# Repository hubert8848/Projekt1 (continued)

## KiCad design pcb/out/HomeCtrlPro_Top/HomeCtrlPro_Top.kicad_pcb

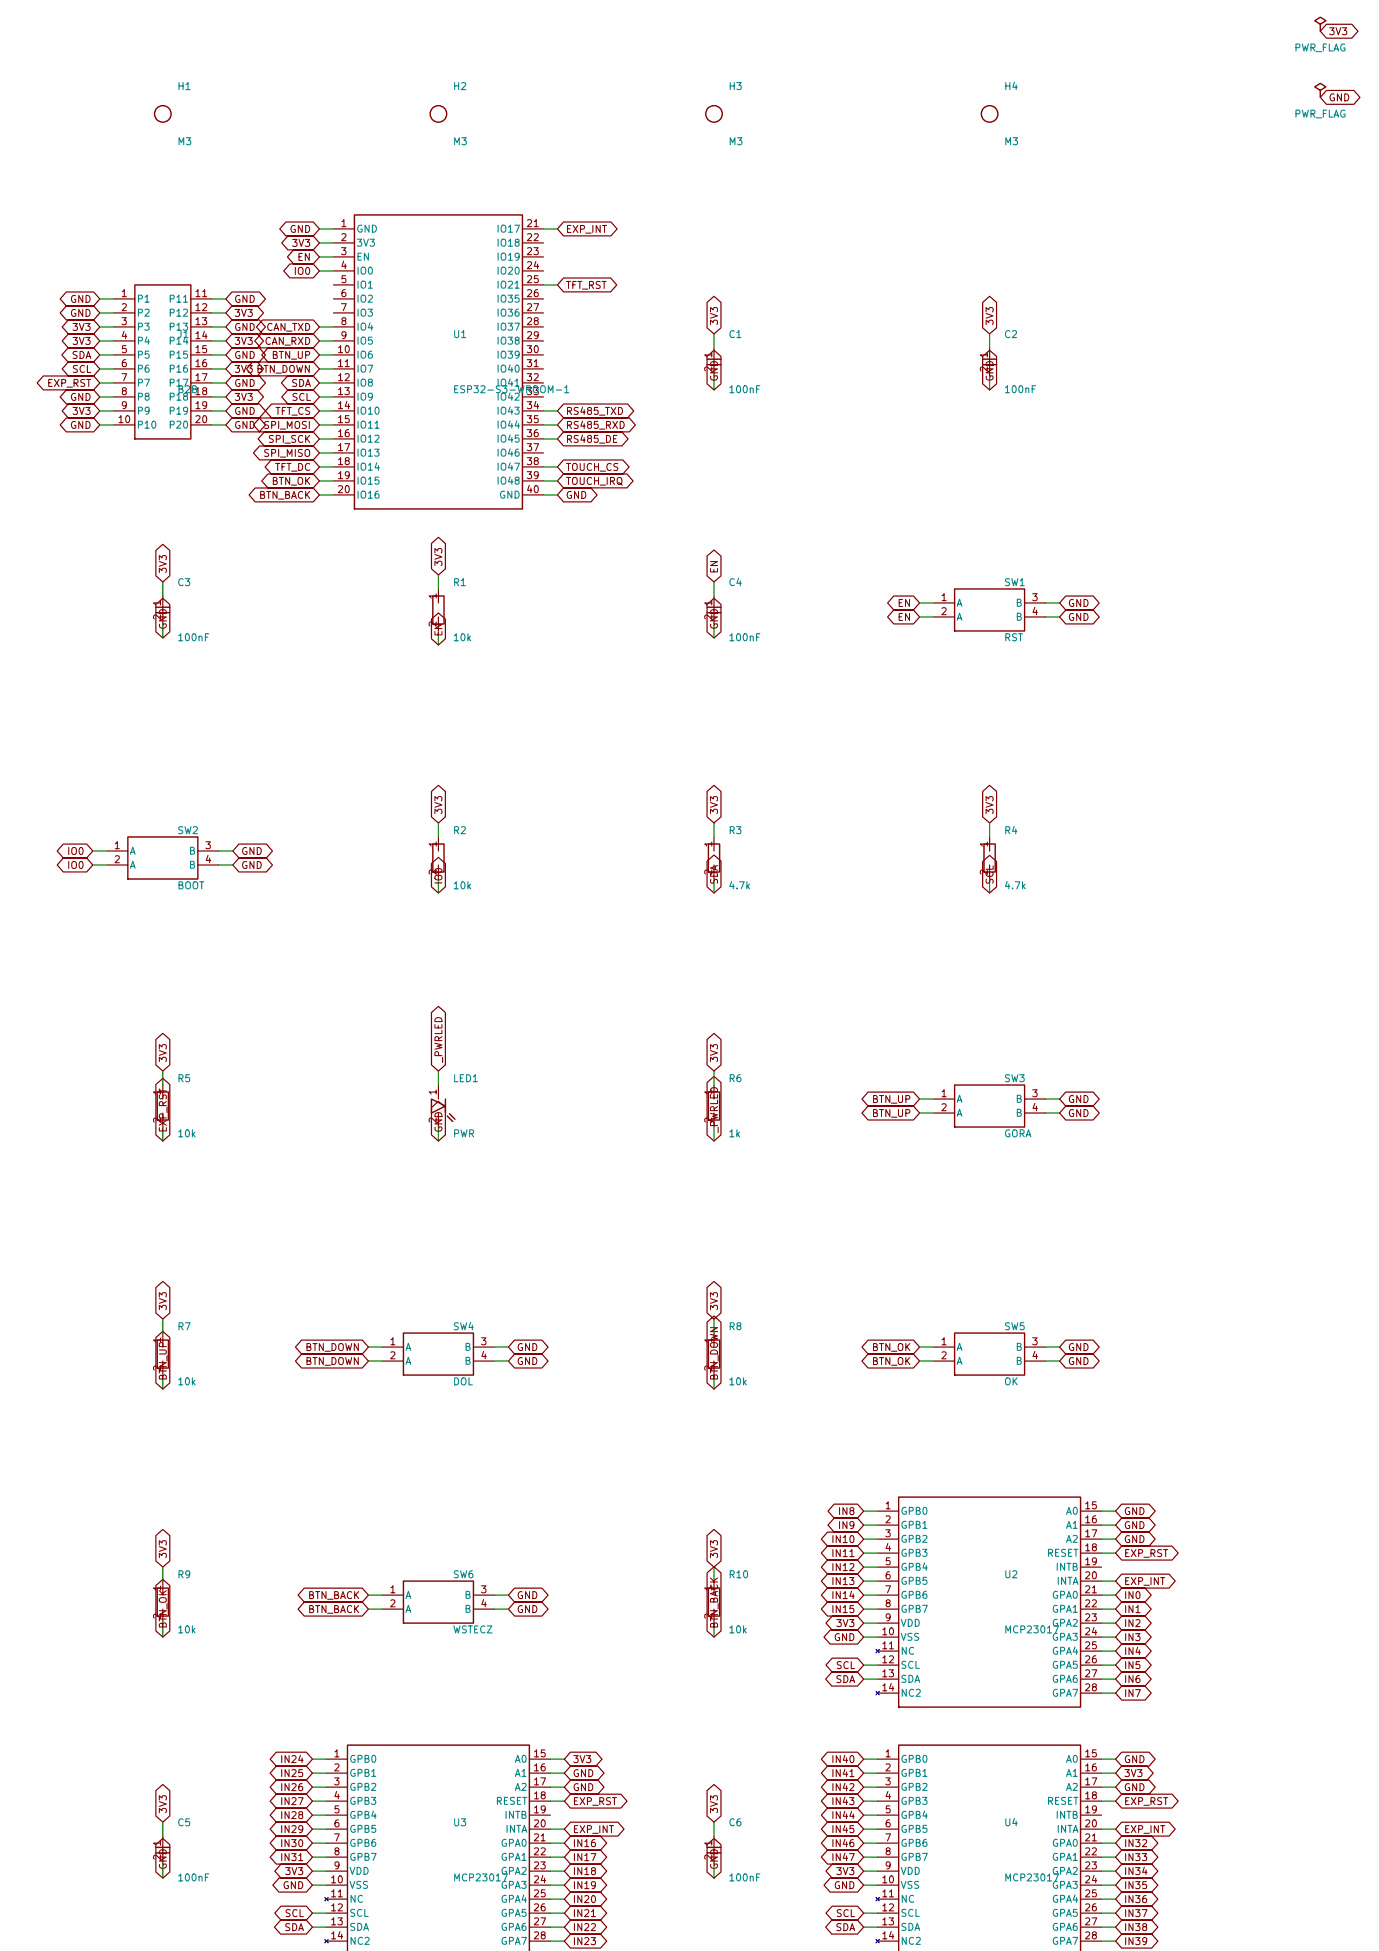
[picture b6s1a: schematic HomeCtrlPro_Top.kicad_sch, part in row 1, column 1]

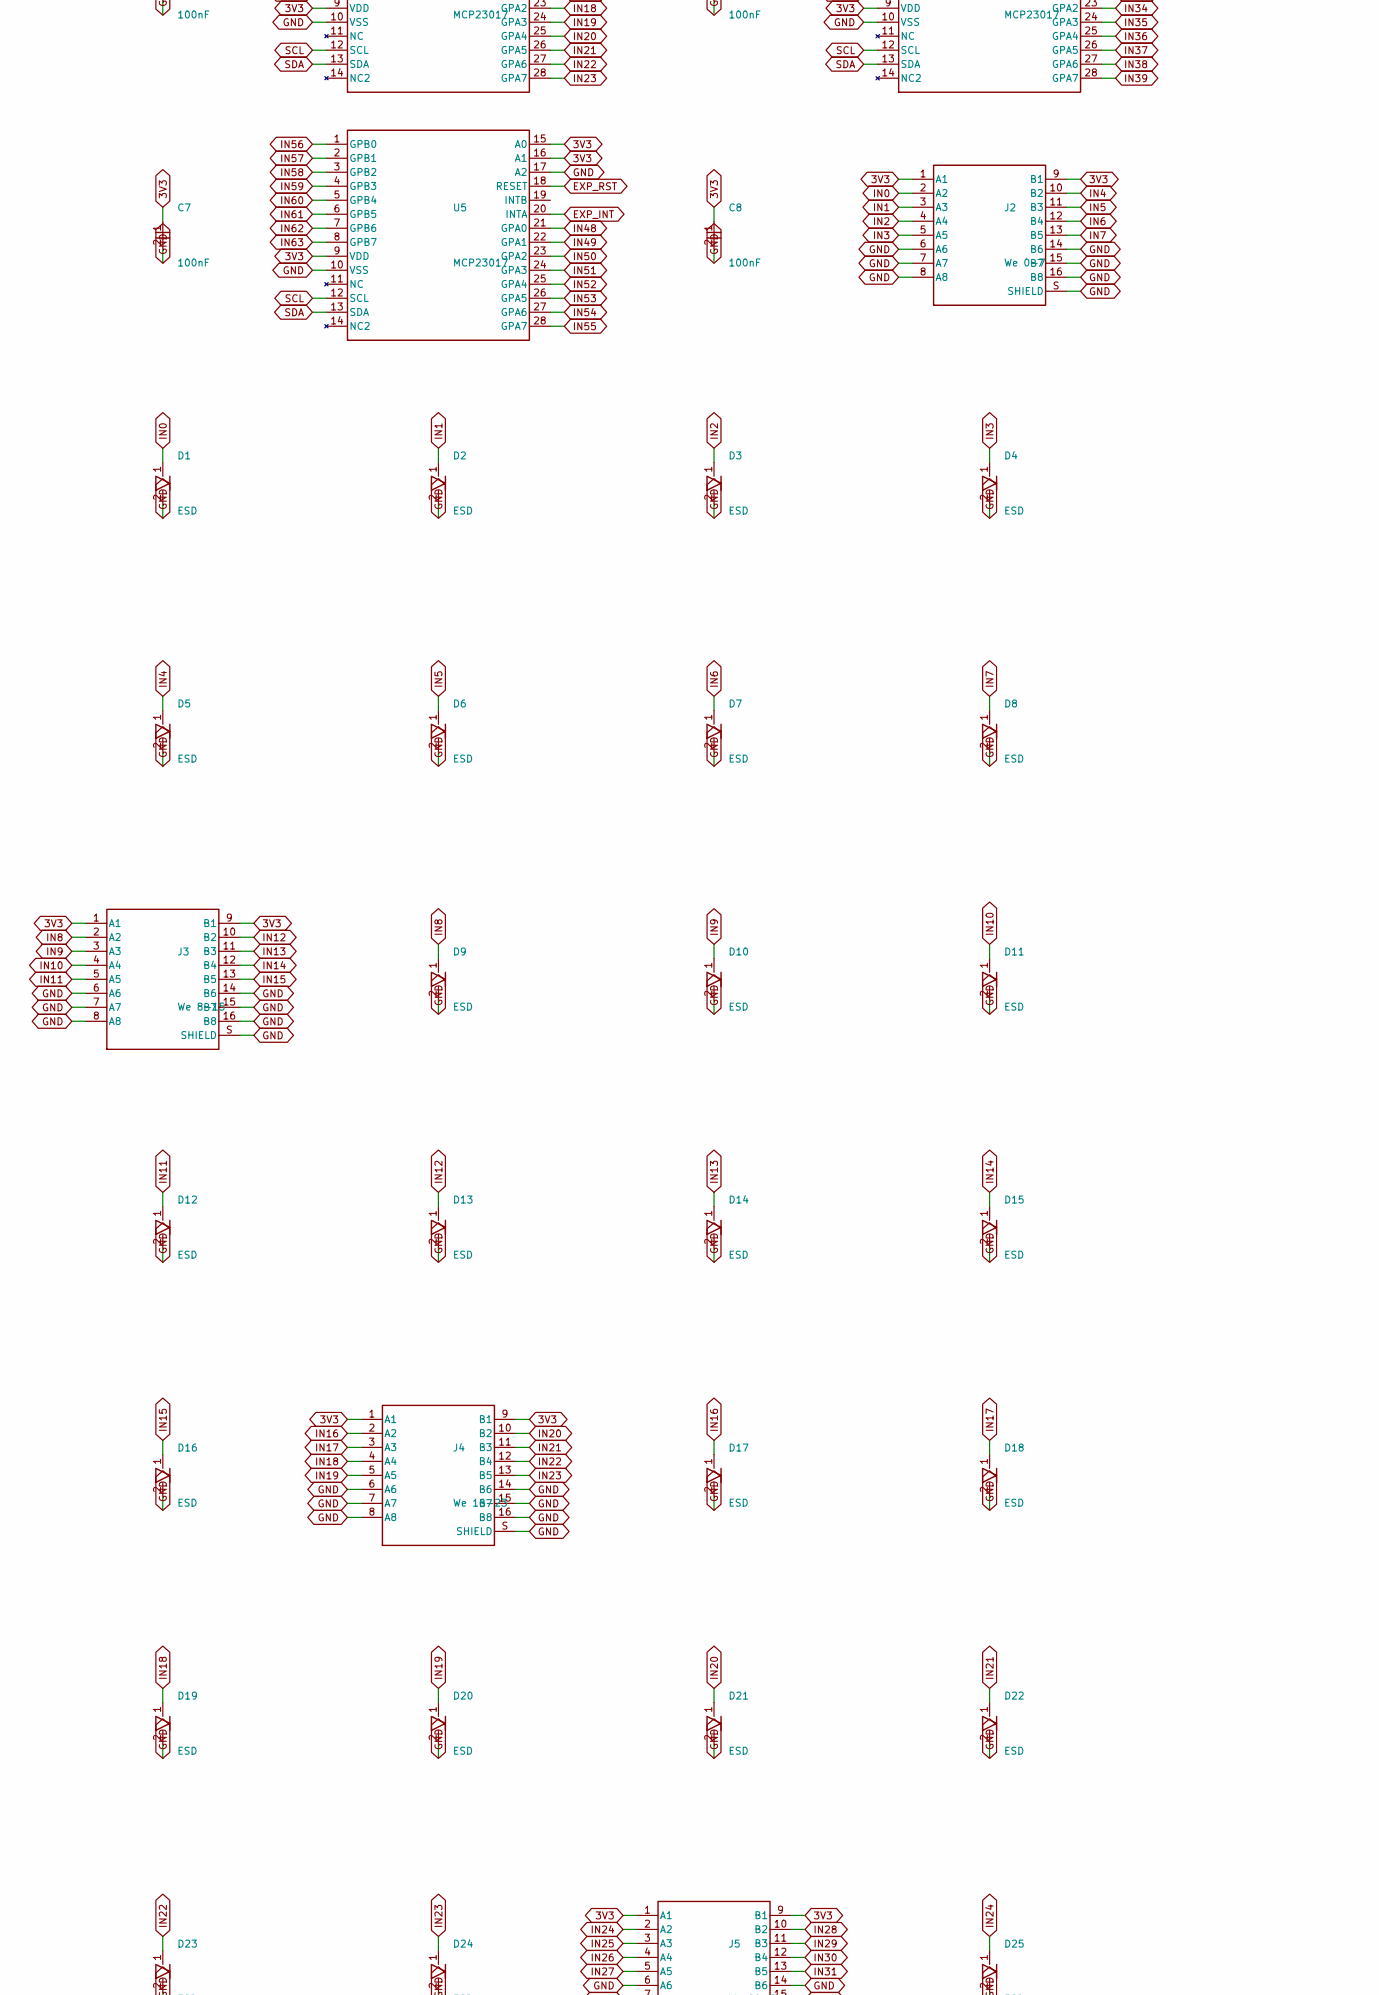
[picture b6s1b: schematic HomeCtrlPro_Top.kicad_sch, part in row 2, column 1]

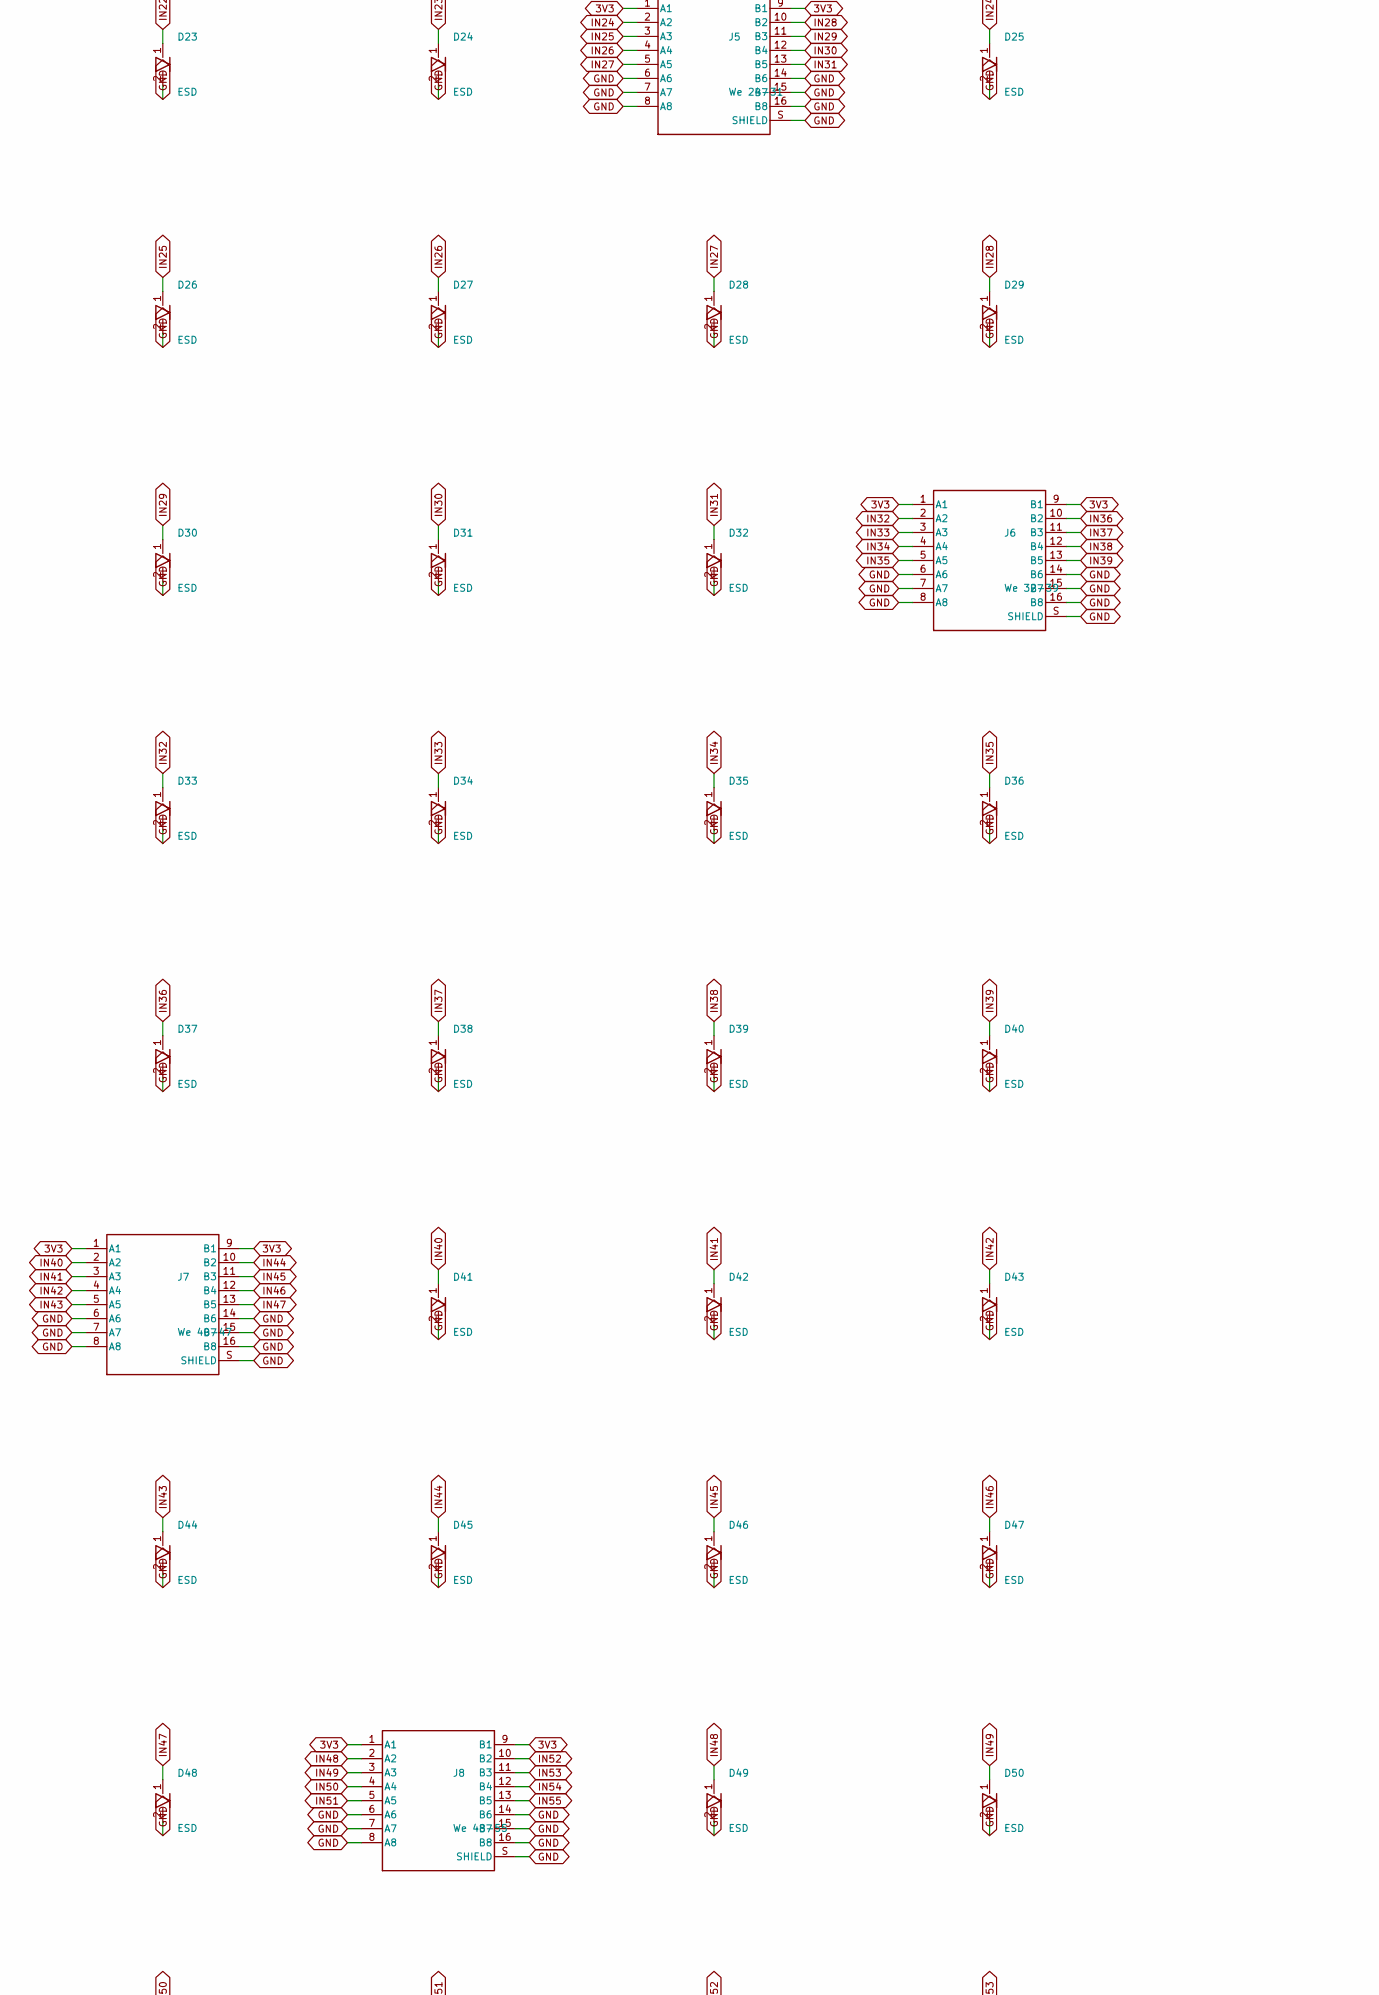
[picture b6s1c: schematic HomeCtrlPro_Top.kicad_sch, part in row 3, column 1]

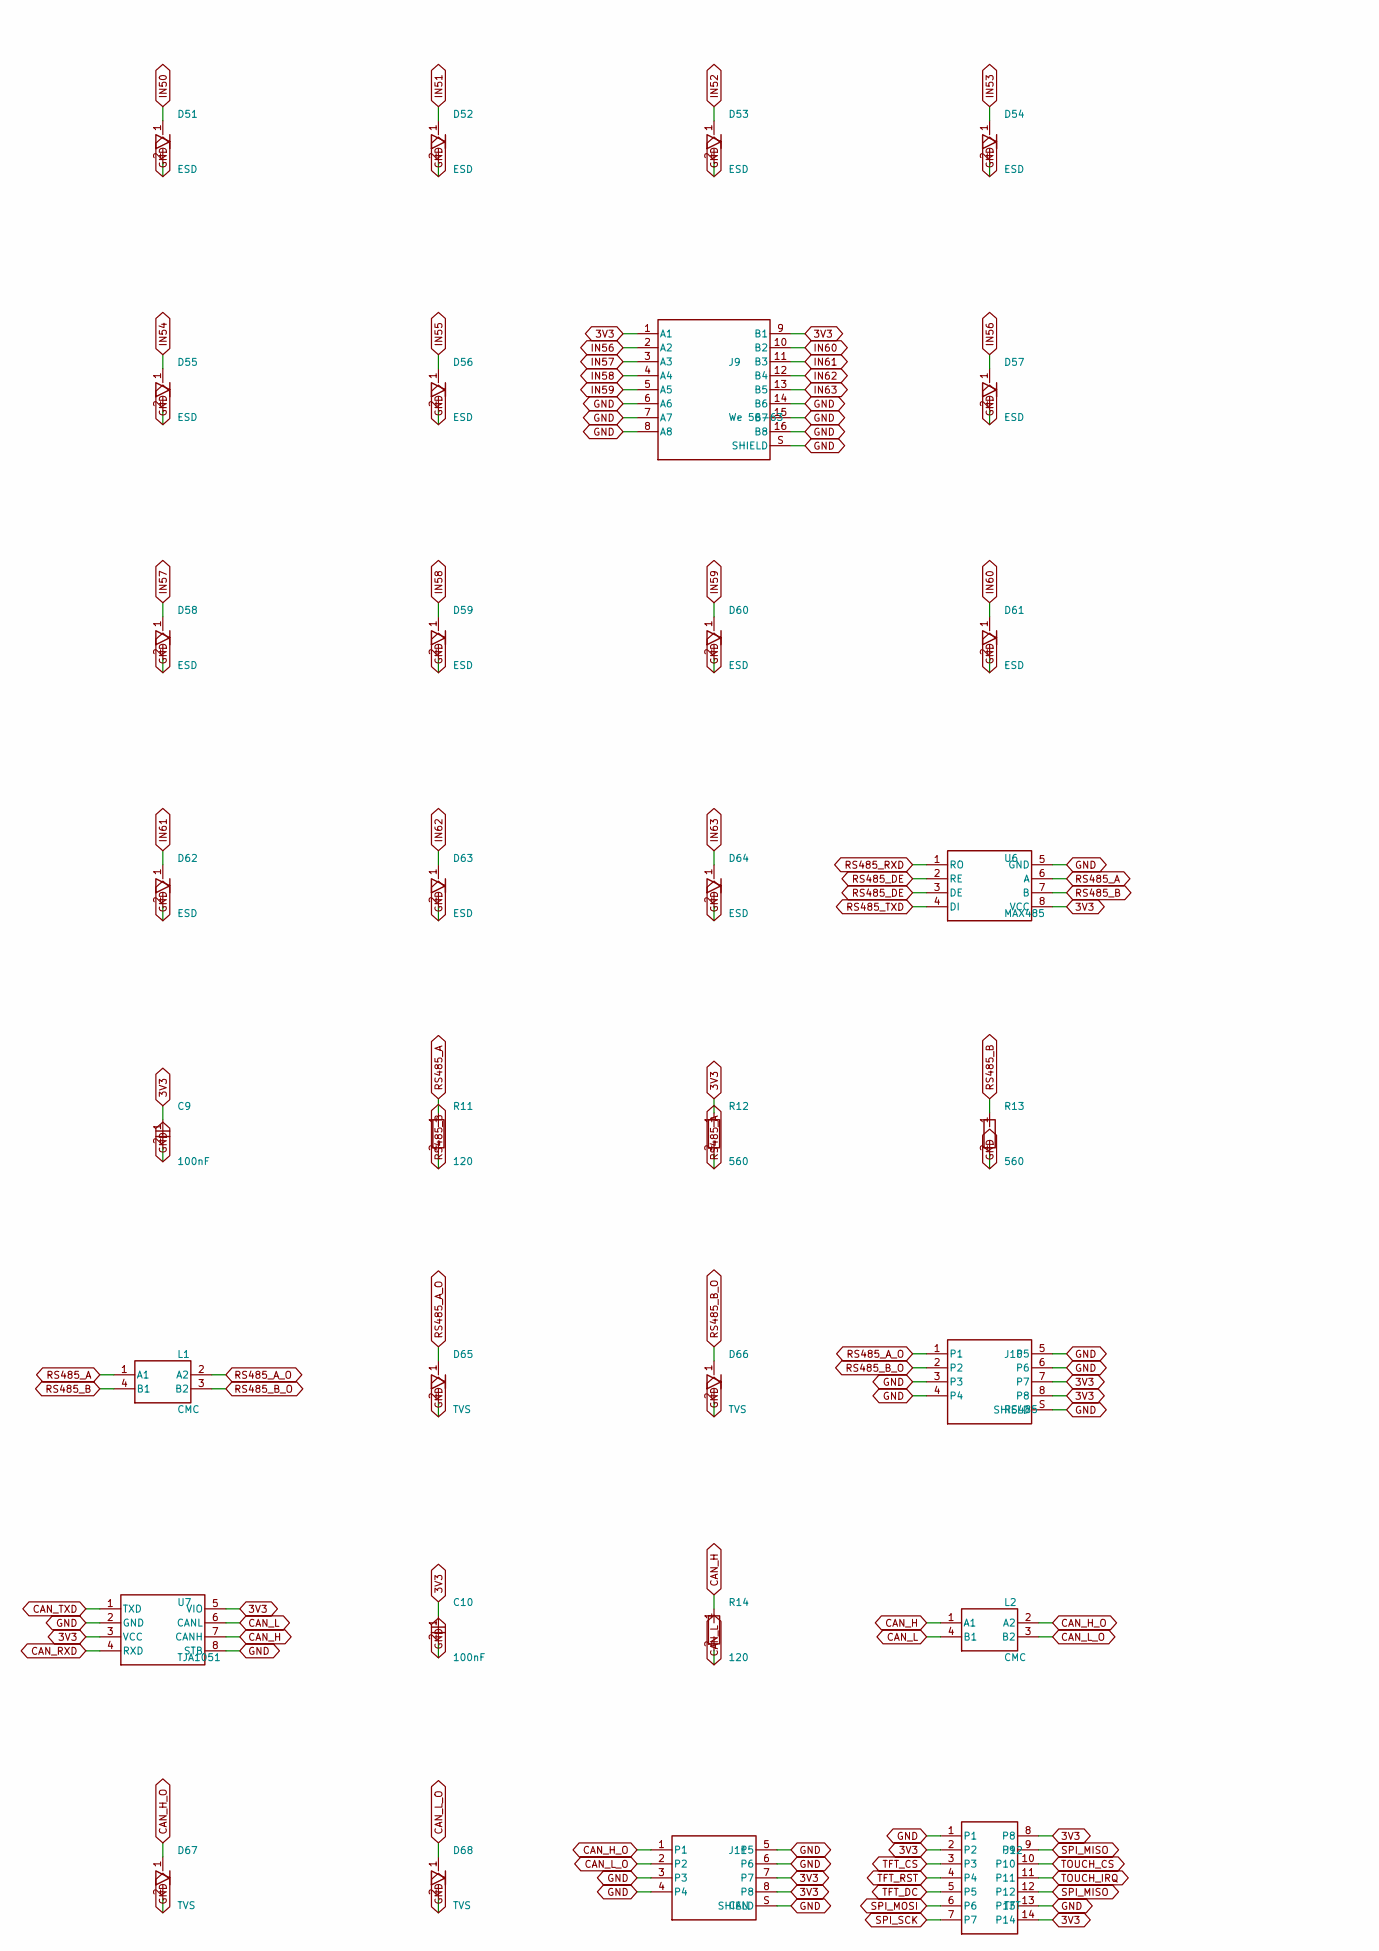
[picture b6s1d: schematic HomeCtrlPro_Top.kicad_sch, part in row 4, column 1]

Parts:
C1, C2, C3, C4, C5, C6, C7, C8, C9, C10: 100nF; C_0805
D1, D2, D3, D4, D5, D6, D7, D8, D9, D10, D11, D12, D13, D14, D15, D16, D17, D18, D19, D20, D21, D22, D23, D24, D25, D26, D27, D28, D29, D30, D31, D32, D33, D34, D35, D36, D37, D38, D39, D40, D41, D42, D43, D44, D45, D46, D47, D48, D49, D50, D51, D52, D53, D54, D55, D56, D57, D58, D59, D60, D61, D62, D63, D64: ESD; D_SOD-323
D65, D66, D67, D68: TVS; D_SOD-323
H1, H2, H3, H4: M3; MountingHole_M3
J1: B2B; Header_2x10
J2: We 0-7; RJ45_Dual
J3: We 8-15; RJ45_Dual
J4: We 16-23; RJ45_Dual
J5: We 24-31; RJ45_Dual
J6: We 32-39; RJ45_Dual
J7: We 40-47; RJ45_Dual
J8: We 48-55; RJ45_Dual
J9: We 56-63; RJ45_Dual
J10: RS485; RJ45_8P8C
J11: CAN; RJ45_8P8C
J12: TFT; Header_2x07
L1, L2: CMC; CMC_4
LED1: PWR; LED_0805
R1, R2, R5, R7, R8, R9, R10: 10k; R_0805
R3, R4: 4.7k; R_0805
R6: 1k; R_0805
R11, R14: 120; R_0805
R12, R13: 560; R_0805
SW1: RST; SW_Push_6mm
SW2: BOOT; SW_Push_6mm
SW3: GORA; SW_Push_6mm
SW4: DOL; SW_Push_6mm
SW5: OK; SW_Push_6mm
SW6: WSTECZ; SW_Push_6mm
U1: ESP32-S3-WROOM-1
U2, U3, U4, U5: MCP23017; SOIC-28
U6: MAX485; SOIC-8
U7: TJA1051; SOIC-8

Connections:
3V3: C1.1, C2.1, C3.1, C5.1, C6.1, C7.1, C8.1, C9.1, C10.1, J1.3, J1.4, J1.9, J1.12, J1.14, J1.16, J1.18, J2.1 (A1), J2.9 (B1), J3.1 (A1), J3.9 (B1), J4.1 (A1), J4.9 (B1), J5.1 (A1), J5.9 (B1), J6.1 (A1), J6.9 (B1), J7.1 (A1), J7.9 (B1), J8.1 (A1), J8.9 (B1), J9.1 (A1), J9.9 (B1), J10.7, J10.8, J11.7, J11.8, J12.2, J12.8, J12.14, R1.1, R2.1, R3.1, R4.1, R5.1, R6.1, R7.1, R8.1, R9.1, R10.1, R12.1, U1.2 (3V3), U2.9 (VDD), U3.9 (VDD), U3.15 (A0), U4.9 (VDD), U4.16 (A1), U5.9 (VDD), U5.15 (A0), U5.16 (A1), U6.8 (VCC), U7.3 (VCC), U7.5 (VIO)
BTN_BACK: R10.2, SW6.1 (A), SW6.2 (A), U1.20 (IO16)
BTN_DOWN: R8.2, SW4.1 (A), SW4.2 (A), U1.11 (IO7)
BTN_OK: R9.2, SW5.1 (A), SW5.2 (A), U1.19 (IO15)
BTN_UP: R7.2, SW3.1 (A), SW3.2 (A), U1.10 (IO6)
CAN_H: L2.1 (A1), R14.1, U7.7 (CANH)
CAN_H_O: D67.1, J11.1, L2.2 (A2)
CAN_L: L2.4 (B1), R14.2, U7.6 (CANL)
CAN_L_O: D68.1, J11.2, L2.3 (B2)
CAN_RXD: U1.9 (IO5), U7.4 (RXD)
CAN_TXD: U1.8 (IO4), U7.1 (TXD)
EN: C4.1, R1.2, SW1.1 (A), SW1.2 (A), U1.3 (EN)
EXP_INT: U1.21 (IO17), U2.20 (INTA), U3.20 (INTA), U4.20 (INTA), U5.20 (INTA)
EXP_RST: J1.7, R5.2, U2.18 (RESET), U3.18 (RESET), U4.18 (RESET), U5.18 (RESET)
GND: C1.2, C2.2, C3.2, C4.2, C5.2, C6.2, C7.2, C8.2, C9.2, C10.2, D1.2, D2.2, D3.2, D4.2, D5.2, D6.2, D7.2, D8.2, D9.2, D10.2, D11.2, D12.2, D13.2, D14.2, D15.2, D16.2, D17.2, D18.2, D19.2, D20.2, D21.2, D22.2, D23.2, D24.2, D25.2, D26.2, D27.2, D28.2, D29.2, D30.2, D31.2, D32.2, D33.2, D34.2, D35.2, D36.2, D37.2, D38.2, D39.2, D40.2, D41.2, D42.2, D43.2, D44.2, D45.2, D46.2, D47.2, D48.2, D49.2, D50.2, D51.2, D52.2, D53.2, D54.2, D55.2, D56.2, D57.2, D58.2, D59.2, D60.2, D61.2, D62.2, D63.2, D64.2, D65.2, D66.2, D67.2, D68.2, J1.1, J1.2, J1.8, J1.10, J1.11, J1.13, J1.15, J1.17, J1.19, J1.20, J2.6 (A6), J2.7 (A7), J2.8 (A8), J2.14 (B6), J2.15 (B7), J2.16 (B8), J2.S (SHIELD), J3.6 (A6), J3.7 (A7), J3.8 (A8), J3.14 (B6), J3.15 (B7), J3.16 (B8), J3.S (SHIELD), J4.6 (A6), J4.7 (A7), J4.8 (A8), J4.14 (B6), J4.15 (B7), J4.16 (B8), J4.S (SHIELD), J5.6 (A6), J5.7 (A7), J5.8 (A8), J5.14 (B6), J5.15 (B7), J5.16 (B8), J5.S (SHIELD), J6.6 (A6), J6.7 (A7), J6.8 (A8), J6.14 (B6), J6.15 (B7), J6.16 (B8), J6.S (SHIELD), J7.6 (A6), J7.7 (A7), J7.8 (A8), J7.14 (B6), J7.15 (B7), J7.16 (B8), J7.S (SHIELD), J8.6 (A6), J8.7 (A7), J8.8 (A8), J8.14 (B6), J8.15 (B7), J8.16 (B8), J8.S (SHIELD), J9.6 (A6), J9.7 (A7), J9.8 (A8), J9.14 (B6), J9.15 (B7), J9.16 (B8), J9.S (SHIELD), J10.3, J10.4, J10.5, J10.6, J10.S (SHIELD), J11.3, J11.4, J11.5, J11.6, J11.S (SHIELD), J12.1, J12.13, LED1.2, R13.2, SW1.3 (B), SW1.4 (B), SW2.3 (B), SW2.4 (B), SW3.3 (B), SW3.4 (B), SW4.3 (B), SW4.4 (B), SW5.3 (B), SW5.4 (B), SW6.3 (B), SW6.4 (B), U1.1 (GND), U1.40 (GND), U2.10 (VSS), U2.15 (A0), U2.16 (A1), U2.17 (A2), U3.10 (VSS), U3.16 (A1), U3.17 (A2), U4.10 (VSS), U4.15 (A0), U4.17 (A2), U5.10 (VSS), U5.17 (A2), U6.5 (GND), U7.2 (GND), U7.8 (STB)
IN0: D1.1, J2.2 (A2), U2.21 (GPA0)
IN1: D2.1, J2.3 (A3), U2.22 (GPA1)
IN2: D3.1, J2.4 (A4), U2.23 (GPA2)
IN3: D4.1, J2.5 (A5), U2.24 (GPA3)
IN4: D5.1, J2.10 (B2), U2.25 (GPA4)
IN5: D6.1, J2.11 (B3), U2.26 (GPA5)
IN6: D7.1, J2.12 (B4), U2.27 (GPA6)
IN7: D8.1, J2.13 (B5), U2.28 (GPA7)
IN8: D9.1, J3.2 (A2), U2.1 (GPB0)
IN9: D10.1, J3.3 (A3), U2.2 (GPB1)
IN10: D11.1, J3.4 (A4), U2.3 (GPB2)
IN11: D12.1, J3.5 (A5), U2.4 (GPB3)
IN12: D13.1, J3.10 (B2), U2.5 (GPB4)
IN13: D14.1, J3.11 (B3), U2.6 (GPB5)
IN14: D15.1, J3.12 (B4), U2.7 (GPB6)
IN15: D16.1, J3.13 (B5), U2.8 (GPB7)
IN16: D17.1, J4.2 (A2), U3.21 (GPA0)
IN17: D18.1, J4.3 (A3), U3.22 (GPA1)
IN18: D19.1, J4.4 (A4), U3.23 (GPA2)
IN19: D20.1, J4.5 (A5), U3.24 (GPA3)
IN20: D21.1, J4.10 (B2), U3.25 (GPA4)
IN21: D22.1, J4.11 (B3), U3.26 (GPA5)
IN22: D23.1, J4.12 (B4), U3.27 (GPA6)
IN23: D24.1, J4.13 (B5), U3.28 (GPA7)
IN24: D25.1, J5.2 (A2), U3.1 (GPB0)
IN25: D26.1, J5.3 (A3), U3.2 (GPB1)
IN26: D27.1, J5.4 (A4), U3.3 (GPB2)
IN27: D28.1, J5.5 (A5), U3.4 (GPB3)
IN28: D29.1, J5.10 (B2), U3.5 (GPB4)
IN29: D30.1, J5.11 (B3), U3.6 (GPB5)
IN30: D31.1, J5.12 (B4), U3.7 (GPB6)
IN31: D32.1, J5.13 (B5), U3.8 (GPB7)
IN32: D33.1, J6.2 (A2), U4.21 (GPA0)
IN33: D34.1, J6.3 (A3), U4.22 (GPA1)
IN34: D35.1, J6.4 (A4), U4.23 (GPA2)
IN35: D36.1, J6.5 (A5), U4.24 (GPA3)
IN36: D37.1, J6.10 (B2), U4.25 (GPA4)
IN37: D38.1, J6.11 (B3), U4.26 (GPA5)
IN38: D39.1, J6.12 (B4), U4.27 (GPA6)
IN39: D40.1, J6.13 (B5), U4.28 (GPA7)
IN40: D41.1, J7.2 (A2), U4.1 (GPB0)
IN41: D42.1, J7.3 (A3), U4.2 (GPB1)
IN42: D43.1, J7.4 (A4), U4.3 (GPB2)
IN43: D44.1, J7.5 (A5), U4.4 (GPB3)
IN44: D45.1, J7.10 (B2), U4.5 (GPB4)
IN45: D46.1, J7.11 (B3), U4.6 (GPB5)
IN46: D47.1, J7.12 (B4), U4.7 (GPB6)
IN47: D48.1, J7.13 (B5), U4.8 (GPB7)
IN48: D49.1, J8.2 (A2), U5.21 (GPA0)
IN49: D50.1, J8.3 (A3), U5.22 (GPA1)
IN50: D51.1, J8.4 (A4), U5.23 (GPA2)
IN51: D52.1, J8.5 (A5), U5.24 (GPA3)
IN52: D53.1, J8.10 (B2), U5.25 (GPA4)
IN53: D54.1, J8.11 (B3), U5.26 (GPA5)
IN54: D55.1, J8.12 (B4), U5.27 (GPA6)
IN55: D56.1, J8.13 (B5), U5.28 (GPA7)
IN56: D57.1, J9.2 (A2), U5.1 (GPB0)
IN57: D58.1, J9.3 (A3), U5.2 (GPB1)
IN58: D59.1, J9.4 (A4), U5.3 (GPB2)
IN59: D60.1, J9.5 (A5), U5.4 (GPB3)
IN60: D61.1, J9.10 (B2), U5.5 (GPB4)
IN61: D62.1, J9.11 (B3), U5.6 (GPB5)
IN62: D63.1, J9.12 (B4), U5.7 (GPB6)
IN63: D64.1, J9.13 (B5), U5.8 (GPB7)
IO0: R2.2, SW2.1 (A), SW2.2 (A), U1.4 (IO0)
RS485_A: L1.1 (A1), R11.1, R12.2, U6.6 (A)
RS485_A_O: D65.1, J10.1, L1.2 (A2)
RS485_B: L1.4 (B1), R11.2, R13.1, U6.7 (B)
RS485_B_O: D66.1, J10.2, L1.3 (B2)
RS485_DE: U1.36 (IO45), U6.2 (RE), U6.3 (DE)
RS485_RXD: U1.35 (IO44), U6.1 (RO)
RS485_TXD: U1.34 (IO43), U6.4 (DI)
SCL: J1.6, R4.2, U1.13 (IO9), U2.12 (SCL), U3.12 (SCL), U4.12 (SCL), U5.12 (SCL)
SDA: J1.5, R3.2, U1.12 (IO8), U2.13 (SDA), U3.13 (SDA), U4.13 (SDA), U5.13 (SDA)
SPI_MISO: J12.9, J12.12, U1.17 (IO13)
SPI_MOSI: J12.6, U1.15 (IO11)
SPI_SCK: J12.7, U1.16 (IO12)
TFT_CS: J12.3, U1.14 (IO10)
TFT_DC: J12.5, U1.18 (IO14)
TFT_RST: J12.4, U1.25 (IO21)
TOUCH_CS: J12.10, U1.38 (IO47)
TOUCH_IRQ: J12.11, U1.39 (IO48)
_PWRLED: LED1.1, R6.2

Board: 2 copper layers, 124 parts (0 on the bottom side), 98 nets, no tracks yet.

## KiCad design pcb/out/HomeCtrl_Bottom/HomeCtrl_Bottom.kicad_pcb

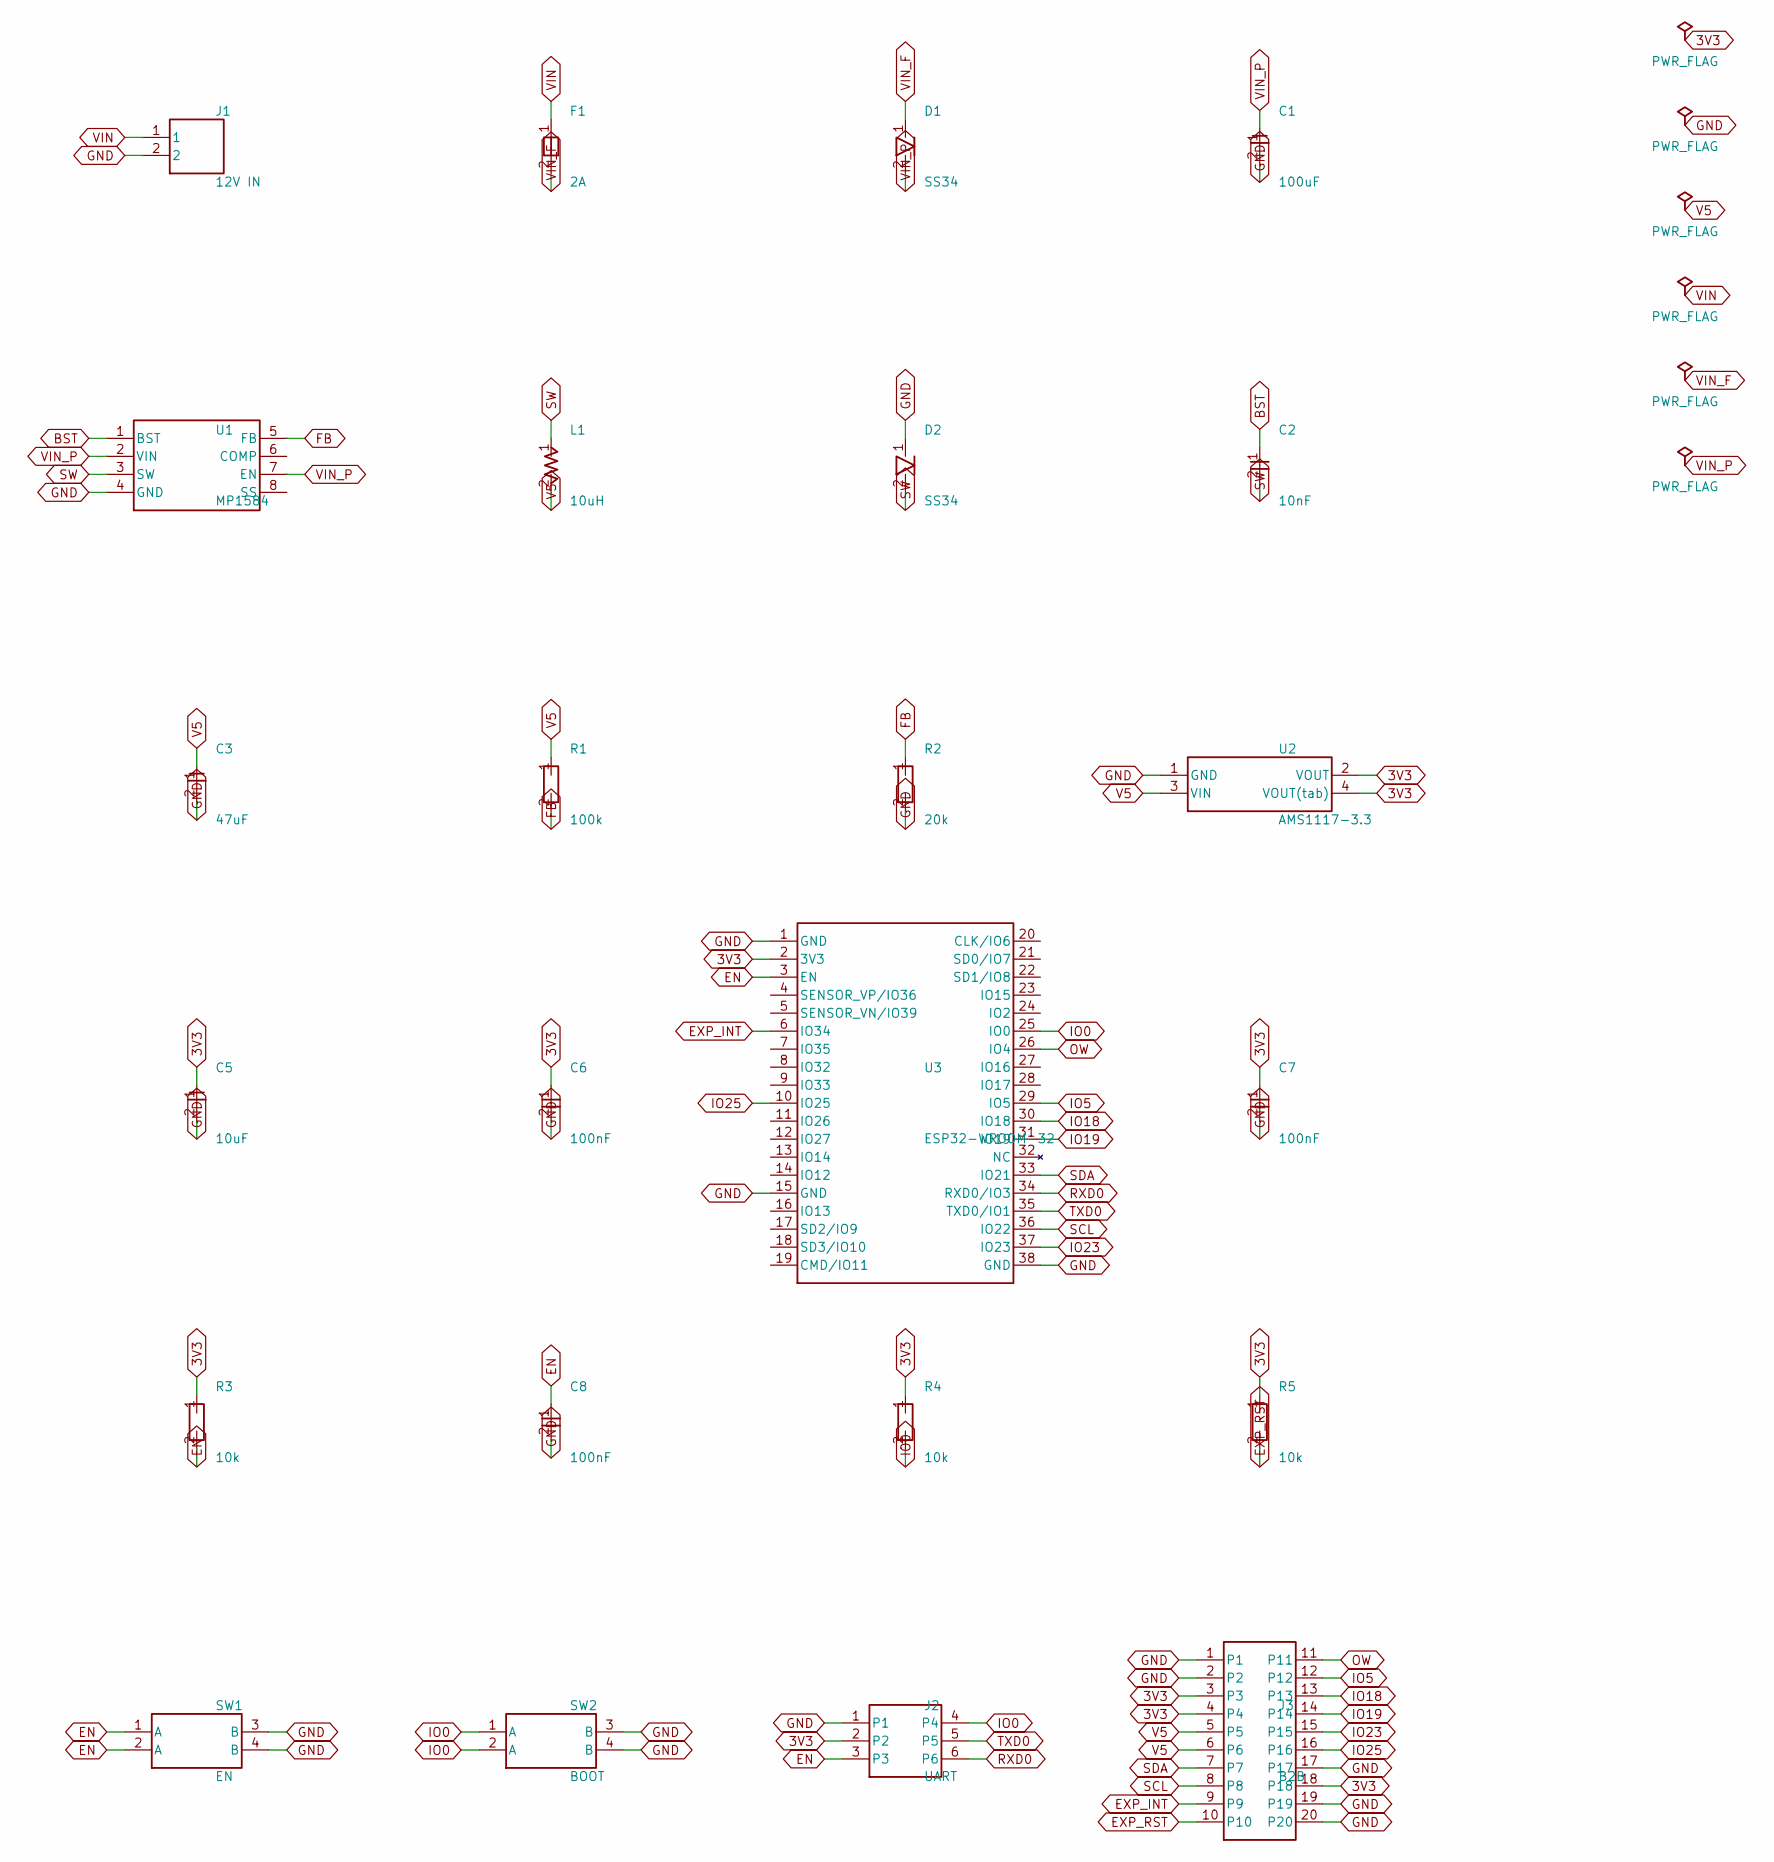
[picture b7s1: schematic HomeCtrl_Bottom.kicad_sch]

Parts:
C1: 100uF; CP_1206
C2: 10nF; C_0805
C3: 47uF; CP_1206
C5: 10uF; CP_1206
C6, C7, C8: 100nF; C_0805
D1, D2: SS34; D_SMA
F1: 2A; F_1206
J1: 12V IN; ScrewTerminal_1x02
J2: UART; Header_1x06
J3: B2B; Header_2x10
L1: 10uH; L_6x6
R1: 100k; R_0805
R2: 20k; R_0805
R3, R4, R5: 10k; R_0805
SW1: EN; SW_Push_6mm
SW2: BOOT; SW_Push_6mm
U1: MP1584; SOIC-8
U2: AMS1117-3.3; SOT-223
U3: ESP32-WROOM-32

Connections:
3V3: C5.1, C6.1, C7.1, J2.2, J3.3, J3.4, J3.18, R3.1, R4.1, R5.1, U2.2 (VOUT), U2.4 (VOUT(tab)), U3.2 (3V3)
BST: C2.1, U1.1 (BST)
EN: C8.1, J2.3, R3.2, SW1.1 (A), SW1.2 (A), U3.3 (EN)
EXP_INT: J3.9, U3.6 (IO34)
EXP_RST: J3.10, R5.2
FB: R1.2, R2.1, U1.5 (FB)
GND: C1.2, C3.2, C5.2, C6.2, C7.2, C8.2, D2.1, J1.2, J2.1, J3.1, J3.2, J3.17, J3.19, J3.20, R2.2, SW1.3 (B), SW1.4 (B), SW2.3 (B), SW2.4 (B), U1.4 (GND), U2.1 (GND), U3.1 (GND), U3.15 (GND), U3.38 (GND)
IO0: J2.4, R4.2, SW2.1 (A), SW2.2 (A), U3.25 (IO0)
IO5: J3.12, U3.29 (IO5)
IO18: J3.13, U3.30 (IO18)
IO19: J3.14, U3.31 (IO19)
IO23: J3.15, U3.37 (IO23)
IO25: J3.16, U3.10 (IO25)
OW: J3.11, U3.26 (IO4)
RXD0: J2.6, U3.34 (RXD0/IO3)
SCL: J3.8, U3.36 (IO22)
SDA: J3.7, U3.33 (IO21)
SW: C2.2, D2.2, L1.1, U1.3 (SW)
TXD0: J2.5, U3.35 (TXD0/IO1)
V5: C3.1, J3.5, J3.6, L1.2, R1.1, U2.3 (VIN)
VIN: F1.1, J1.1
VIN_F: D1.1, F1.2
VIN_P: C1.1, D1.2, U1.2 (VIN), U1.7 (EN)

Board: 2 copper layers, 24 parts (0 on the bottom side), 23 nets, no tracks yet.
